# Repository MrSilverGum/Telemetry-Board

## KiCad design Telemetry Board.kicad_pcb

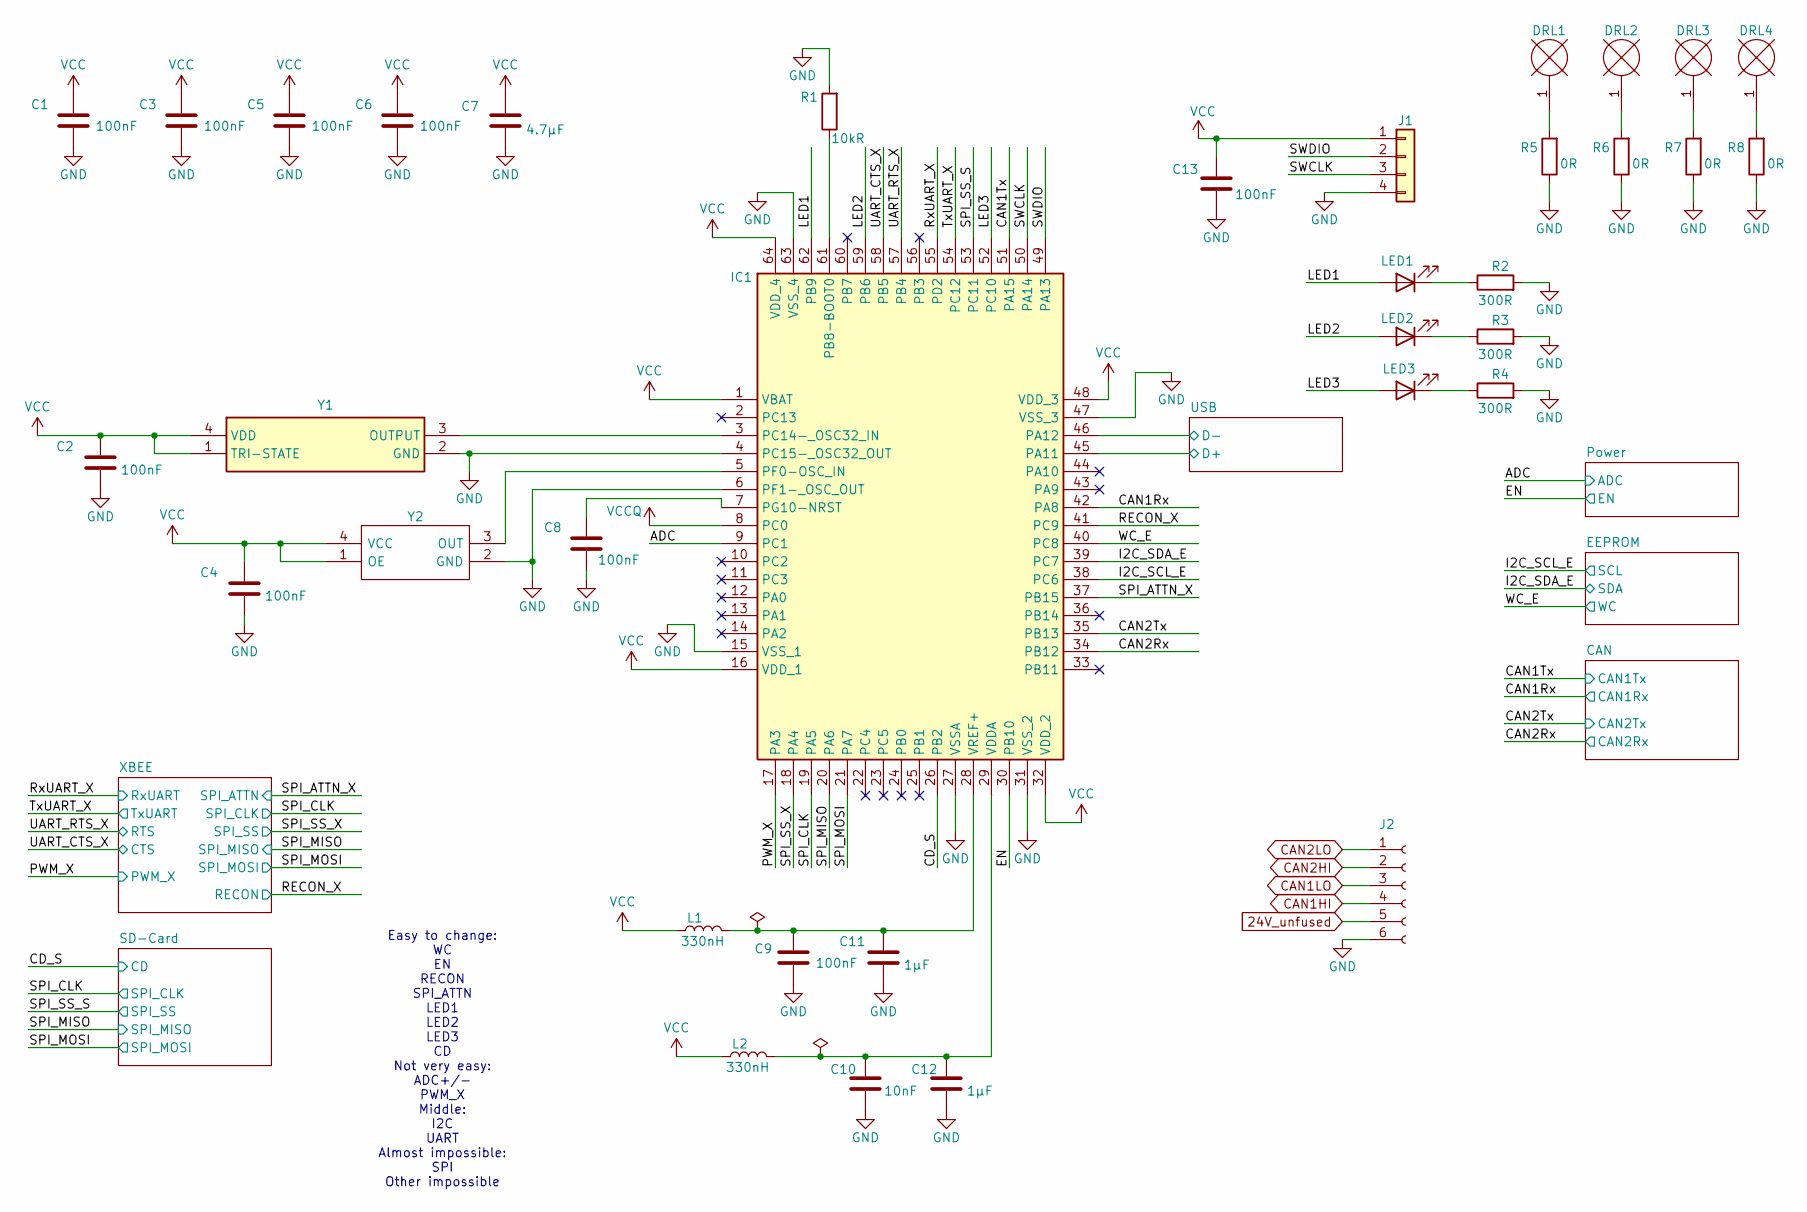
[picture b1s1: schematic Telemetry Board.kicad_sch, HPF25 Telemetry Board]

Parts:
C1, C2, C3, C4, C5, C6, C8, C9, C13: 100nF; C_0805_2012Metric_Pad1.18x1.45mm_HandSolder; TOLERANCE (FILL IN AS +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 10%
C7: 4.7µF; C_0805_2012Metric_Pad1.18x1.45mm_HandSolder; TOLERANCE (FILL IN AS +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 10%
C10: 10nF; C_0805_2012Metric_Pad1.18x1.45mm_HandSolder; TOLERANCE (FILL IN AS +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 10%
C11, C12: 1µF; C_0805_2012Metric_Pad1.18x1.45mm_HandSolder; TOLERANCE (FILL IN AS +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 10%
DRL1, DRL2, DRL3, DRL4: HOLE4.28.4; MountingHole_2.2mm_M2_Pad
IC1: STM32G484RET6; QFP50P1200X1200X160-64N; Mouser Part Number 511-STM32G484RET6
J1: Conn_01x04; PinSocket_1x04_P2.54mm_Vertical
J2: Conn_01x06_Socket; PinHeader_1x06_P2.54mm_Vertical
L1, L2: 330nH; L_0805_2012Metric_Pad1.15x1.40mm_HandSolder; TOLERANCE 20%
LED1: XL-2012UPC; LED_0805_2012Metric_Pad1.15x1.40mm_HandSolder
LED2: SML-210YTT86M; LED_0805_2012Metric_Pad1.15x1.40mm_HandSolder; MANUFACTURER_PART_NUMBER SML-210YTT86M
LED3: 150080BS75000; LED_0805_2012Metric_Pad1.15x1.40mm_HandSolder; MANUFACTURER_PART_NUMBER SZYY0805B
R1: 10kR; R_0805_2012Metric_Pad1.20x1.40mm_HandSolder
R2, R3, R4: 300R; R_0805_2012Metric_Pad1.20x1.40mm_HandSolder; POWER RATING 400mW; TOLERANCE 5%
R5, R6, R7, R8: 0R; R_0805_2012Metric_Pad1.20x1.40mm_HandSolder
Y1: ECS-327MVATX-3-CN-TR3; ECS327MVATX3CNTR; Mouser Part Number 520-327MVATX-3-CNTR3
Y2: SG-8018CE_8.0000M-TJHPA3; SG8018CE80000MTJHPA3; Mouser Part Number 732-CE8M-TJHPA3

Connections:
24V_unfused: J2.5; also elsewhere on the board
/ADC: IC1.9 (PC1); also elsewhere on the board
/CAN1Rx: IC1.42 (PA8); also elsewhere on the board
/CAN1Tx: IC1.51 (PA15); also elsewhere on the board
/CAN2Rx: IC1.34 (PB12); also elsewhere on the board
/CAN2Tx: IC1.35 (PB13); also elsewhere on the board
/CD_S: IC1.26 (PB2); also elsewhere on the board
/EN: IC1.30 (PB10); also elsewhere on the board
/I2C_SCL_E: IC1.38 (PC6); also elsewhere on the board
/I2C_SDA_E: IC1.39 (PC7); also elsewhere on the board
/LED1: IC1.62 (PB9), LED1.2 (A)
/LED2: IC1.59 (PB6), LED2.2 (A)
/LED3: IC1.52 (PC10), LED3.2 (A)
/PWM_X: IC1.17 (PA3); also elsewhere on the board
/RECON_X: IC1.41 (PC9); also elsewhere on the board
/RxUART_X: IC1.55 (PD2); also elsewhere on the board
/SPI_ATTN_X: IC1.37 (PB15); also elsewhere on the board
/SPI_CLK: IC1.19 (PA5); also elsewhere on the board
/SPI_MISO: IC1.20 (PA6); also elsewhere on the board
/SPI_MOSI: IC1.21 (PA7); also elsewhere on the board
/SPI_SS_S: IC1.53 (PC11); also elsewhere on the board
/SPI_SS_X: IC1.18 (PA4); also elsewhere on the board
/SWCLK: IC1.50 (PA14), J1.3
/SWDIO: IC1.49 (PA13), J1.2
/TxUART_X: IC1.54 (PC12); also elsewhere on the board
/UART_CTS_X: IC1.58 (PB5); also elsewhere on the board
/UART_RTS_X: IC1.57 (PB4); also elsewhere on the board
/USB/D+: IC1.45 (PA11); also elsewhere on the board
/USB/D-: IC1.46 (PA12); also elsewhere on the board
/WC_E: IC1.40 (PC8); also elsewhere on the board
CAN1HI: J2.4; also elsewhere on the board
CAN1LO: J2.3; also elsewhere on the board
CAN2HI: J2.2; also elsewhere on the board
CAN2LO: J2.1; also elsewhere on the board
GND: C1.2, C2.2, C3.2, C4.2, C5.2, C6.2, C7.2, C8.2, C9.2, C10.2, C11.2, C12.2, C13.2, IC1.4 (PC15-_OSC32_OUT), IC1.6 (PF1-_OSC_OUT), IC1.15 (VSS_1), IC1.27 (VSSA), IC1.31 (VSS_2), IC1.47 (VSS_3), IC1.63 (VSS_4), J1.4, J2.6, R1.2, R2.2, R3.2, R4.2, R5.1, R6.1, R7.1, R8.1, Y1.2 (GND), Y2.2 (GND); also elsewhere on the board
unnamed: DRL1.1, R5.2
unnamed: DRL2.1, R6.2
unnamed: DRL3.1, R7.2
unnamed: DRL4.1, R8.2
unnamed: IC1.61 (PB8-BOOT0), R1.1
unnamed: IC1.3 (PC14-_OSC32_IN), Y1.3 (OUTPUT)
unnamed: IC1.5 (PF0-OSC_IN), Y2.3 (OUT)
unnamed: C8.1, IC1.7 (PG10-NRST)
unnamed: C10.1, C12.1, IC1.29 (VDDA), L2.2
unnamed: C9.1, C11.1, IC1.28 (VREF+), L1.2
unnamed: LED1.1 (K), R2.1
unnamed: LED2.1 (K), R3.1
unnamed: LED3.1 (K), R4.1
VCC: C1.1, C2.1, C3.1, C4.1, C5.1, C6.1, C7.1, C13.1, IC1.1 (VBAT), IC1.16 (VDD_1), IC1.32 (VDD_2), IC1.48 (VDD_3), IC1.64 (VDD_4), J1.1, L1.1, L2.1, Y1.1 (TRI-STATE), Y1.4 (VDD), Y2.1 (OE), Y2.4 (VCC); also elsewhere on the board
VCCQ: IC1.8 (PC0); also elsewhere on the board

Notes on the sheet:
Easy to change: WC EN RECON SPI_ATTN LED1 LED2 LED3 CD Not very easy: ADC+/- PWM_X Middle: I2C UART Almost impossible: SPI Other impossible

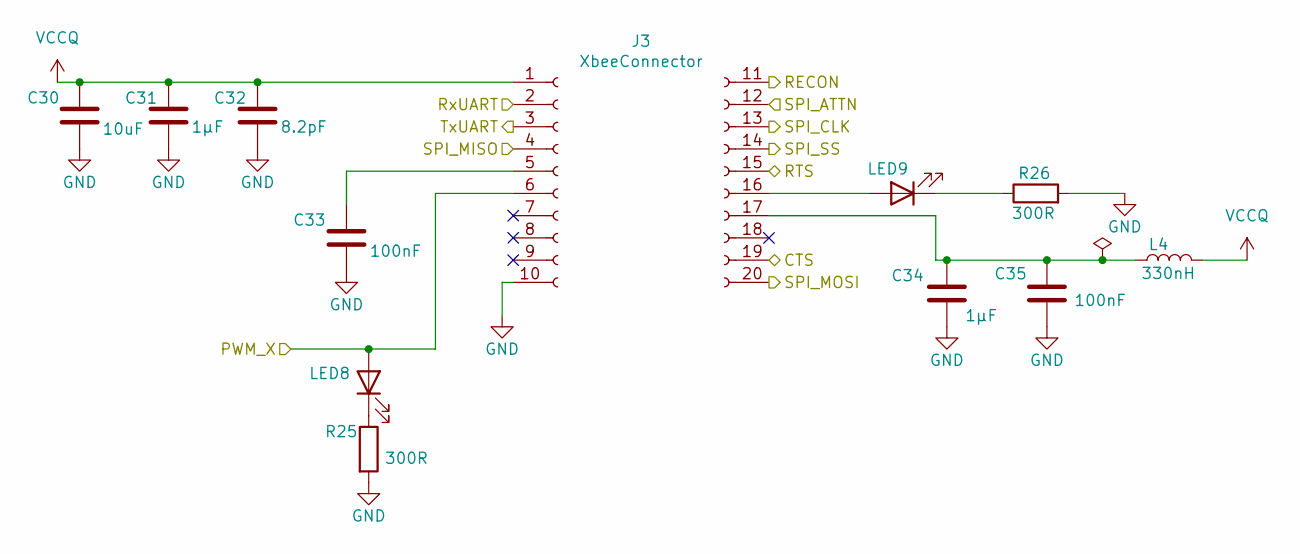
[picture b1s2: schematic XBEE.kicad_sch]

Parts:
C30: 10uF; C_0805_2012Metric_Pad1.18x1.45mm_HandSolder
C31, C34: 1µF; C_0805_2012Metric_Pad1.18x1.45mm_HandSolder; TOLERANCE (FILL IN AS +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 10%
C32: 8.2pF; C_0805_2012Metric_Pad1.18x1.45mm_HandSolder
C33, C35: 100nF; C_0805_2012Metric_Pad1.18x1.45mm_HandSolder; TOLERANCE (FILL IN AS +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 10%
J3: XbeeConnector; XbeeSocket
L4: 330nH; L_0805_2012Metric_Pad1.15x1.40mm_HandSolder; TOLERANCE 20%
LED8: SML-H12D8TT86; LED_0805_2012Metric_Pad1.15x1.40mm_HandSolder; MANUFACTURER_PART_NUMBER SML-H12D8TT86; MOUSER PART NUMBER 755-SML-H12D8TT86
LED9: SMLMN2WB1CW1; LED_0805_2012Metric_Pad1.15x1.40mm_HandSolder; MANUFACTURER_PART_NUMBER SMLMN2WB1CW1; MOUSER PART NUMBER 755-SMLMN2WB1CW1C
R25, R26: 300R; R_0805_2012Metric_Pad1.20x1.40mm_HandSolder; POWER RATING 400mW; TOLERANCE 5%

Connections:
/PWM_X: J3.6, LED8.2 (A); also elsewhere on the board
/RECON_X: J3.11; also elsewhere on the board
/RxUART_X: J3.2; also elsewhere on the board
/SPI_ATTN_X: J3.12; also elsewhere on the board
/SPI_CLK: J3.13; also elsewhere on the board
/SPI_MISO: J3.4; also elsewhere on the board
/SPI_MOSI: J3.20; also elsewhere on the board
/SPI_SS_X: J3.14; also elsewhere on the board
/TxUART_X: J3.3; also elsewhere on the board
/UART_CTS_X: J3.19; also elsewhere on the board
/UART_RTS_X: J3.15; also elsewhere on the board
GND: C30.2, C31.2, C32.2, C33.1, C34.1, C35.2, J3.10, R25.2, R26.2; also elsewhere on the board
unnamed: C33.2, J3.5
unnamed: J3.16, LED9.2 (A)
unnamed: C34.2, C35.1, J3.17, L4.1
unnamed: LED8.1 (K), R25.1
unnamed: LED9.1 (K), R26.1
VCCQ: C30.1, C31.1, C32.1, J3.1, L4.2; also elsewhere on the board

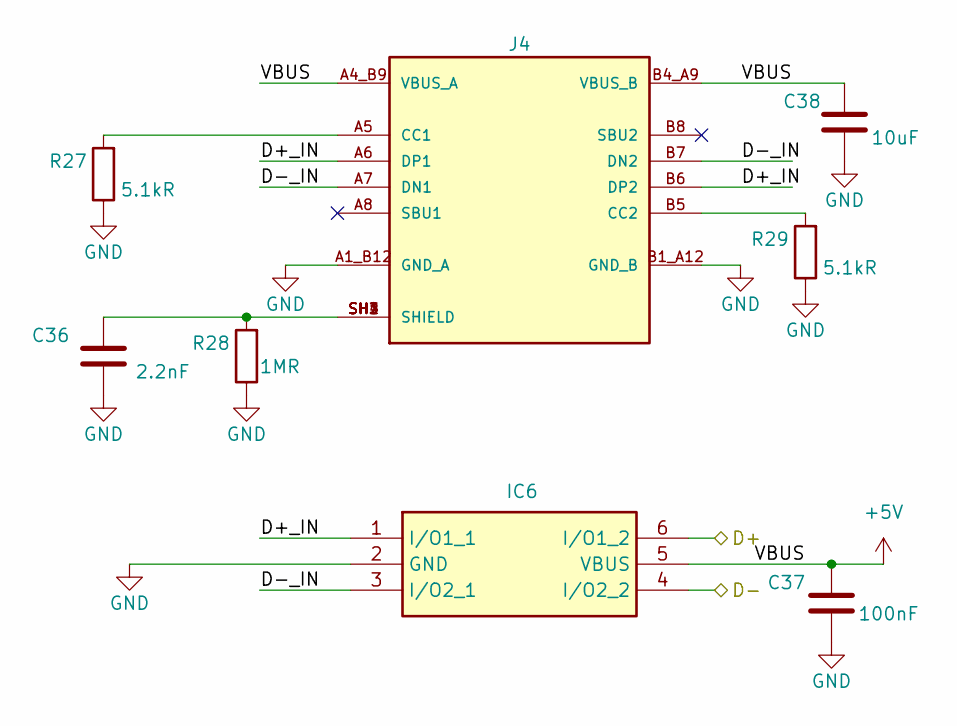
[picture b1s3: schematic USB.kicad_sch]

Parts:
C36: 2.2nF; C_0805_2012Metric_Pad1.18x1.45mm_HandSolder
C37: 100nF; C_0805_2012Metric_Pad1.18x1.45mm_HandSolder; TOLERANCE (FILL IN AS +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 10%
C38: 10uF; C_0805_2012Metric_Pad1.18x1.45mm_HandSolder
IC6: USBLC6-2SC6; SOT95P280X145-6N; Mouser Part Number 511-USBLC6-2SC6
J4: USB4215-03-A_REVA; GCT_USB4215-03-A_REVA; PARTREV A
R27, R29: 5.1kR; R_0805_2012Metric_Pad1.20x1.40mm_HandSolder
R28: 1MR; R_0805_2012Metric_Pad1.20x1.40mm_HandSolder

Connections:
+5V: C37.1, C38.1, IC6.5 (VBUS), J4.A4_B9 (VBUS_A), J4.B4_A9 (VBUS_B); also elsewhere on the board
/USB/D+: IC6.6 (I/O1_2); also elsewhere on the board
/USB/D+_IN: IC6.1 (I/O1_1), J4.A6 (DP1), J4.B6 (DP2)
/USB/D-: IC6.4 (I/O2_2); also elsewhere on the board
/USB/D-_IN: IC6.3 (I/O2_1), J4.A7 (DN1), J4.B7 (DN2)
GND: C36.2, C37.2, C38.2, IC6.2 (GND), J4.A1_B12 (GND_A), J4.B1_A12 (GND_B), R27.1, R28.1, R29.1; also elsewhere on the board
unnamed: C36.1, J4.SH1 (SHIELD), J4.SH2 (SHIELD), J4.SH3 (SHIELD), J4.SH4 (SHIELD), R28.2
unnamed: J4.A5 (CC1), R27.2
unnamed: J4.B5 (CC2), R29.2

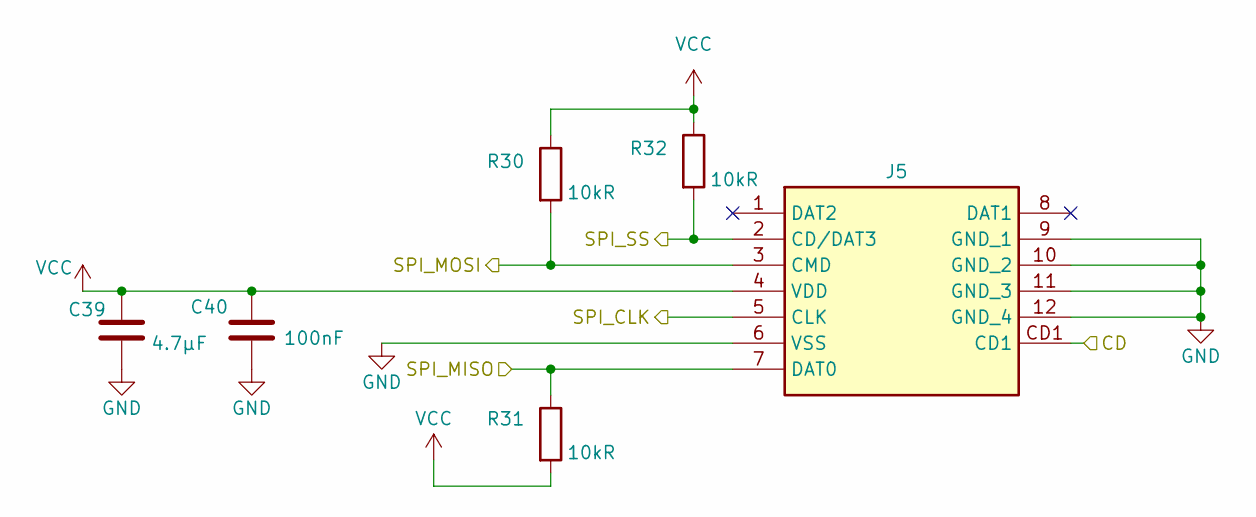
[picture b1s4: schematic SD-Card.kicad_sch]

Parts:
C39: 4.7µF; C_0805_2012Metric_Pad1.18x1.45mm_HandSolder; TOLERANCE (FILL IN AS +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 10%
C40: 100nF; C_0805_2012Metric_Pad1.18x1.45mm_HandSolder; TOLERANCE (FILL IN AS +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 10%
J5: MSD-1-A; MSD1A; Mouser Part Number 179-MSD-1-A
R30, R31, R32: 10kR; R_0805_2012Metric_Pad1.20x1.40mm_HandSolder

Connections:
/CD_S: J5.CD1; also elsewhere on the board
/SPI_CLK: J5.5 (CLK); also elsewhere on the board
/SPI_MISO: J5.7 (DAT0), R31.1; also elsewhere on the board
/SPI_MOSI: J5.3 (CMD), R30.2; also elsewhere on the board
/SPI_SS_S: J5.2 (CD/DAT3), R32.2; also elsewhere on the board
GND: C39.2, C40.2, J5.6 (VSS), J5.9 (GND_1), J5.10 (GND_2), J5.11 (GND_3), J5.12 (GND_4); also elsewhere on the board
VCC: C39.1, C40.1, J5.4 (VDD), R30.1, R31.2, R32.1; also elsewhere on the board

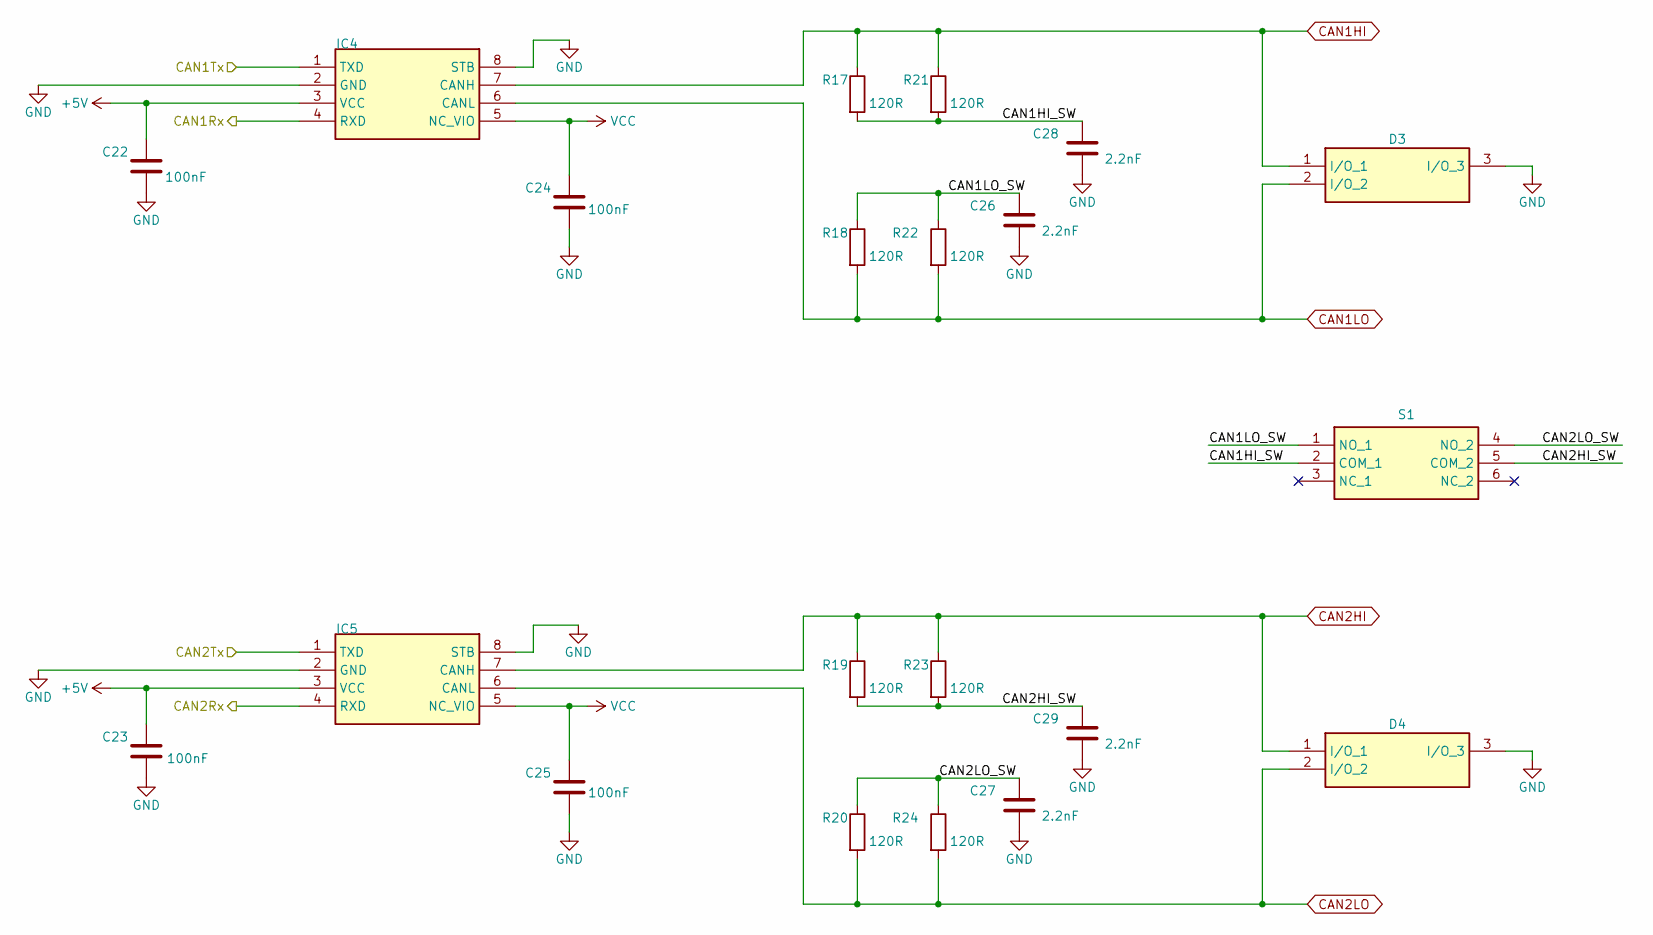
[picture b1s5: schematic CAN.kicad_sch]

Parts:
C22, C23, C24, C25: 100nF; C_0805_2012Metric_Pad1.18x1.45mm_HandSolder; TOLERANCE (FILL IN AS +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 10%
C26, C27, C28, C29: 2.2nF; C_0805_2012Metric_Pad1.18x1.45mm_HandSolder
D3, D4: ESDCAN24-2BLY; SOT95P255X125-3N; Mouser Part Number 511-ESDCAN24-2BLY
IC4, IC5: TCAN1462VDRQ1; SOIC127P600X175-8N; MANUFACTURER_PART_NUMBER TCAN1462VDRQ1; MOUSER PART NUMBER 595-TCAN1462VDRQ1
R17, R18, R19, R20, R21, R22, R23, R24: 120R; R_0805_2012Metric_Pad1.20x1.40mm_HandSolder
S1: CAS-D20TB1; CASD20TB1; Mouser Part Number 229-CAS-D20TB1

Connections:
+5V: C22.1, C23.1, IC4.3 (VCC), IC5.3 (VCC); also elsewhere on the board
/CAN1Rx: IC4.4 (RXD); also elsewhere on the board
/CAN1Tx: IC4.1 (TXD); also elsewhere on the board
/CAN2Rx: IC5.4 (RXD); also elsewhere on the board
/CAN2Tx: IC5.1 (TXD); also elsewhere on the board
/CAN/CAN1HI_SW: C28.1, R17.2, R21.2, S1.2 (COM_1)
/CAN/CAN1LO_SW: C26.1, R18.1, R22.1, S1.1 (NO_1)
/CAN/CAN2HI_SW: C29.1, R19.2, R23.2, S1.5 (COM_2)
/CAN/CAN2LO_SW: C27.1, R20.1, R24.1, S1.4 (NO_2)
CAN1HI: D3.1 (I/O), IC4.7 (CANH), R17.1, R21.1; also elsewhere on the board
CAN1LO: D3.2 (I/O), IC4.6 (CANL), R18.2, R22.2; also elsewhere on the board
CAN2HI: D4.1 (I/O), IC5.7 (CANH), R19.1, R23.1; also elsewhere on the board
CAN2LO: D4.2 (I/O), IC5.6 (CANL), R20.2, R24.2; also elsewhere on the board
GND: C22.2, C23.2, C24.2, C25.2, C26.2, C27.2, C28.2, C29.2, D3.3 (I/O), D4.3 (I/O), IC4.2 (GND), IC4.8 (STB), IC5.2 (GND), IC5.8 (STB); also elsewhere on the board
VCC: C24.1, C25.1, IC4.5 (NC_VIO), IC5.5 (NC_VIO); also elsewhere on the board

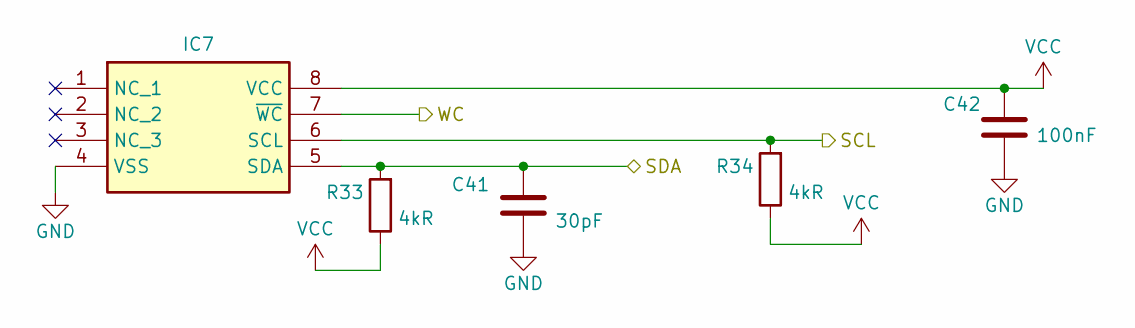
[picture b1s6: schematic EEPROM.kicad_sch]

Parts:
C41: 30pF; C_0805_2012Metric_Pad1.18x1.45mm_HandSolder
C42: 100nF; C_0805_2012Metric_Pad1.18x1.45mm_HandSolder; TOLERANCE (FILL IN AS +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 10%
IC7: M24256E-FMN6TP; SOIC127P600X175-8N; Mouser Part Number 511-M24256E-FMN6TP
R33, R34: 4kR; R_0805_2012Metric_Pad1.20x1.40mm_HandSolder

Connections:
/I2C_SCL_E: IC7.6 (SCL), R34.2; also elsewhere on the board
/I2C_SDA_E: C41.1, IC7.5 (SDA), R33.2; also elsewhere on the board
/WC_E: IC7.7 (~WC); also elsewhere on the board
GND: C41.2, C42.2, IC7.4 (VSS); also elsewhere on the board
VCC: C42.1, IC7.8 (VCC), R33.1, R34.1; also elsewhere on the board

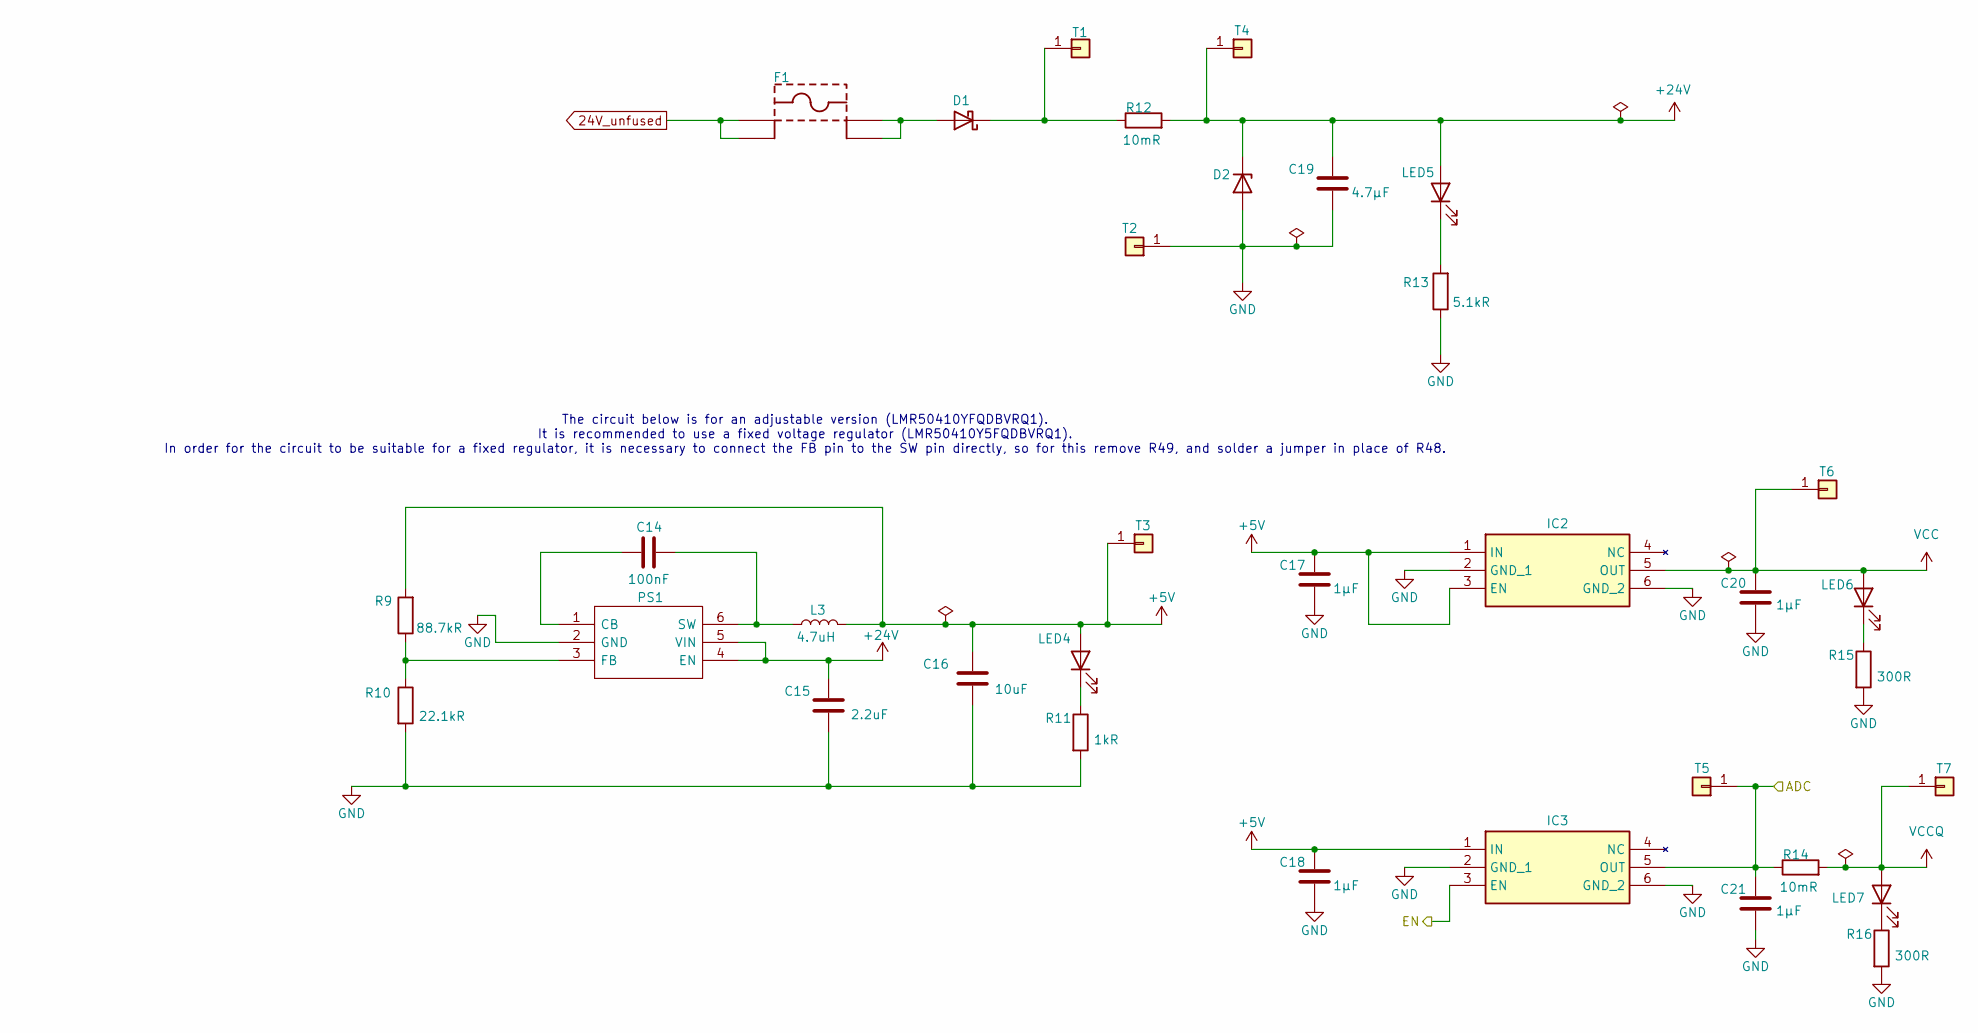
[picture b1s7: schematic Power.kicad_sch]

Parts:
C14: 100nF; C_0805_2012Metric_Pad1.18x1.45mm_HandSolder; TOLERANCE (FILL IN AS +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 10%
C15: 2.2uF; C_0805_2012Metric_Pad1.18x1.45mm_HandSolder
C16: 10uF; C_0805_2012Metric_Pad1.18x1.45mm_HandSolder
C17, C18, C20, C21: 1µF; C_0805_2012Metric_Pad1.18x1.45mm_HandSolder; TOLERANCE (FILL IN AS +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 10%
C19: 4.7µF; C_0805_2012Metric_Pad1.18x1.45mm_HandSolder; TOLERANCE (FILL IN AS +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 10%
D1: SX33L_R1_00001; D_SMA_Handsoldering
D2: 1SMA5934BT3G; D_SMA_Handsoldering; PARTNUMBER 1SMA5934BT3G
F1: 3557-2; VOLTAGE 500V; CURRENT RATING 30A
IC2, IC3: TLV75533PDYDR; Mouser Part Number 595-TLV75533PDYDR
L3: 4.7uH; L_0805_2012Metric_Pad1.15x1.40mm_HandSolder
LED4: SML-210YTT86M; LED_0805_2012Metric_Pad1.15x1.40mm_HandSolder; MANUFACTURER_PART_NUMBER SML-210YTT86M
LED5: SML-210VTT86; LED_0805_2012Metric_Pad1.15x1.40mm_HandSolder; FORWARD VOLTAGE 2V; REVERSE VOLTAGE 4V; MANUFACTURER PART NUMBER SML-210VTT86; MOUSER DESCRIPTION Standard LEDs - SMD RED SMD TRANS LENS
LED6: SML-H12P8TT86; LED_0805_2012Metric_Pad1.15x1.40mm_HandSolder; MANUFACTURER_PART_NUMBER SML-H12P8TT86; MOUSER PART NUMBER 755-SML-H12P8TT86
LED7: 150080BS75000; LED_0805_2012Metric_Pad1.15x1.40mm_HandSolder; MANUFACTURER_PART_NUMBER SZYY0805B
PS1: LMR50410YFQDBVRQ1; SOT95P280X145-6N; Mouser Part Number 595-MR50410YFQDBVRQ1
R9: 88.7kR; R_0805_2012Metric_Pad1.20x1.40mm_HandSolder
R10: 22.1kR; R_0805_2012Metric_Pad1.20x1.40mm_HandSolder
R11: 1kR; R_0805_2012Metric_Pad1.20x1.40mm_HandSolder
R12, R14: 10mR; R_0805_2012Metric_Pad1.20x1.40mm_HandSolder; TOLERANCE 1%
R13: 5.1kR; R_0805_2012Metric_Pad1.20x1.40mm_HandSolder
R15, R16: 300R; R_0805_2012Metric_Pad1.20x1.40mm_HandSolder; POWER RATING 400mW; TOLERANCE 5%
T1, T2, T3, T4, T5, T6, T7: Conn_01x01; TestPoint_THTPad_D1.5mm_Drill0.7mm

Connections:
24V_unfused: F1.1, F1.3; also elsewhere on the board
+5V: C16.1, C17.1, C18.1, IC2.1 (IN), IC2.3 (EN), IC3.1 (IN), L3.2, LED4.2 (A), R9.2, T3.1; also elsewhere on the board
+24V: C15.1, C19.1, D2.1 (K), LED5.2 (A), PS1.4 (EN), PS1.5 (VIN), R12.2, T4.1
/ADC: C21.1, IC3.5 (OUT), R14.1, T5.1; also elsewhere on the board
/EN: IC3.3 (EN); also elsewhere on the board
GND: C15.2, C16.2, C17.2, C18.2, C19.2, C20.2, C21.2, D2.2 (A), IC2.2 (GND_1), IC2.6 (GND_2), IC3.2 (GND_1), IC3.6 (GND_2), PS1.2 (GND), R10.2, R11.2, R13.1, R15.2, R16.2, T2.1; also elsewhere on the board
unnamed: D1.2 (A), F1.2, F1.4
unnamed: D1.1 (K), R12.1, T1.1
unnamed: LED4.1 (K), R11.1
unnamed: LED5.1 (K), R13.2
unnamed: LED6.1 (K), R15.1
unnamed: LED7.1 (K), R16.1
unnamed: C14.1, PS1.1 (CB)
unnamed: PS1.3 (FB), R9.1, R10.1
unnamed: C14.2, L3.1, PS1.6 (SW)
VCC: C20.1, IC2.5 (OUT), LED6.2 (A), T6.1; also elsewhere on the board
VCCQ: LED7.2 (A), R14.2, T7.1; also elsewhere on the board

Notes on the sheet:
The circuit below is for an adjustable version (LMR50410YFQDBVRQ1). It is recommended to use a fixed voltage regulator (LMR50410Y5FQDBVRQ1). In order for the circuit to be suitable for a fixed regulator, it is necessary to connect the FB pin to the SW pin directly, so for this remove R49, and solde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

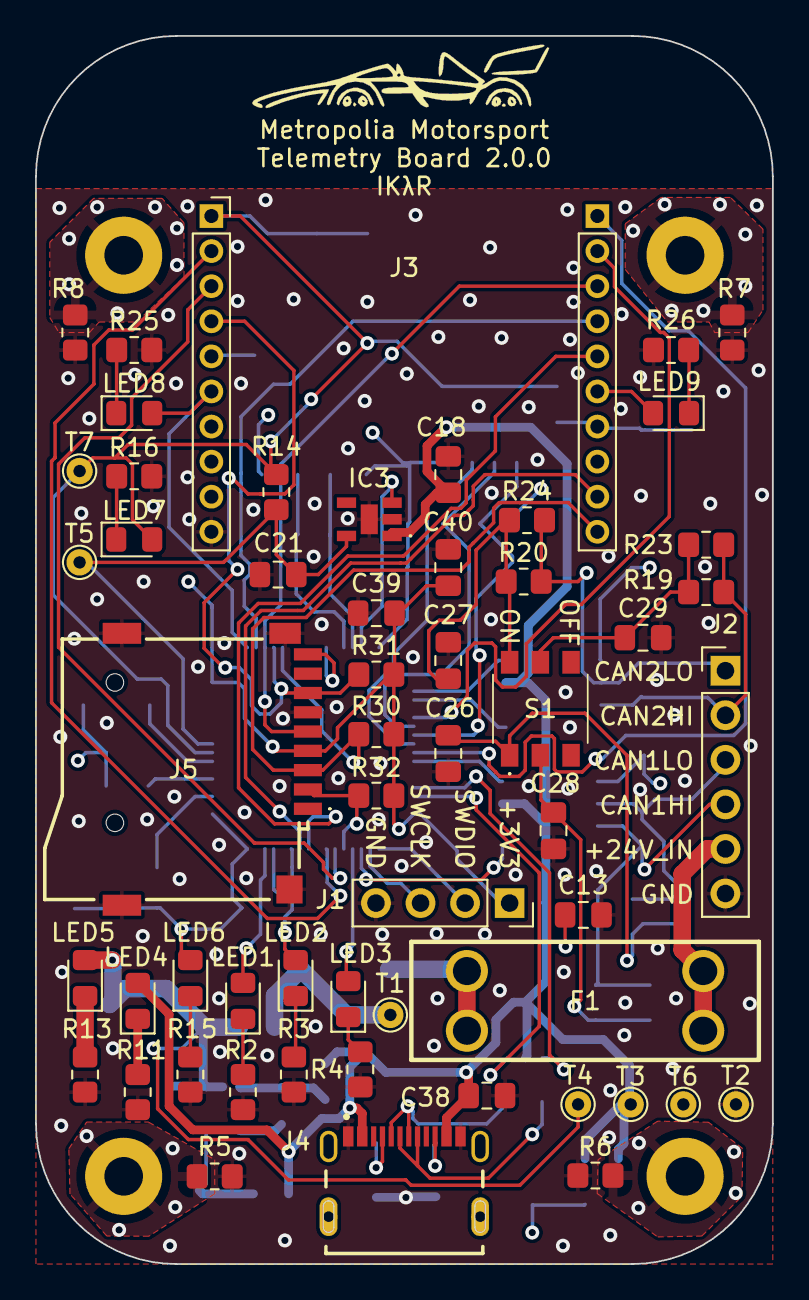
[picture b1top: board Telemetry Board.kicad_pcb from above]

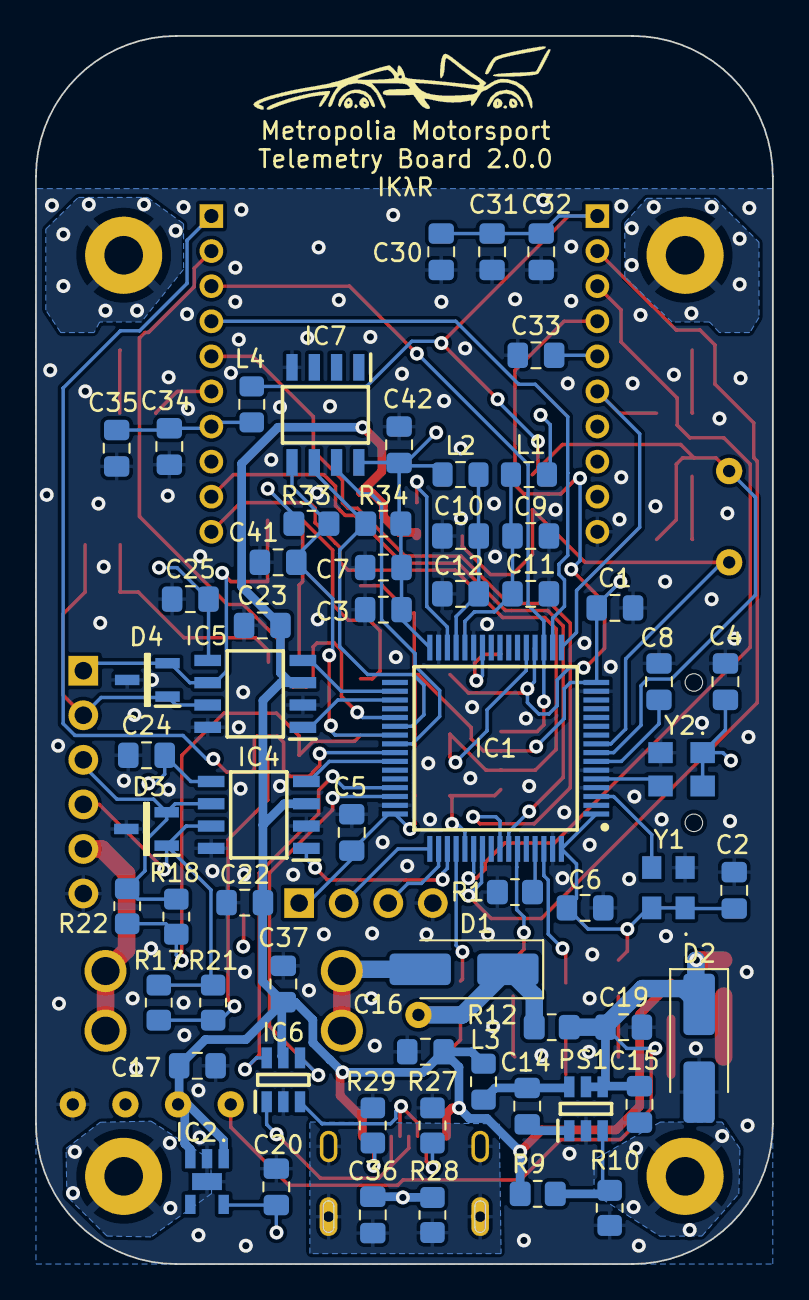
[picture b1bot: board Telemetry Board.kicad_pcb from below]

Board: 4 copper layers, 42.0 x 70.0 mm, 121 parts (62 on the bottom side), 75 nets.

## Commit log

2025-04-17 Initial upload
